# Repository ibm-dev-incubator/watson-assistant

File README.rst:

Watson Home Assistant Raspberry Pi Hat
======================================

This project is a raspberry pi hat that includes an audio codec with an
integrated microphone, speaker. The intent is to use this to leverage the Watson
APIs to create a voice controlled home assistant. In addition to the speakers
there are 4 addressable RGB LEDs that can be used for more user feedback.

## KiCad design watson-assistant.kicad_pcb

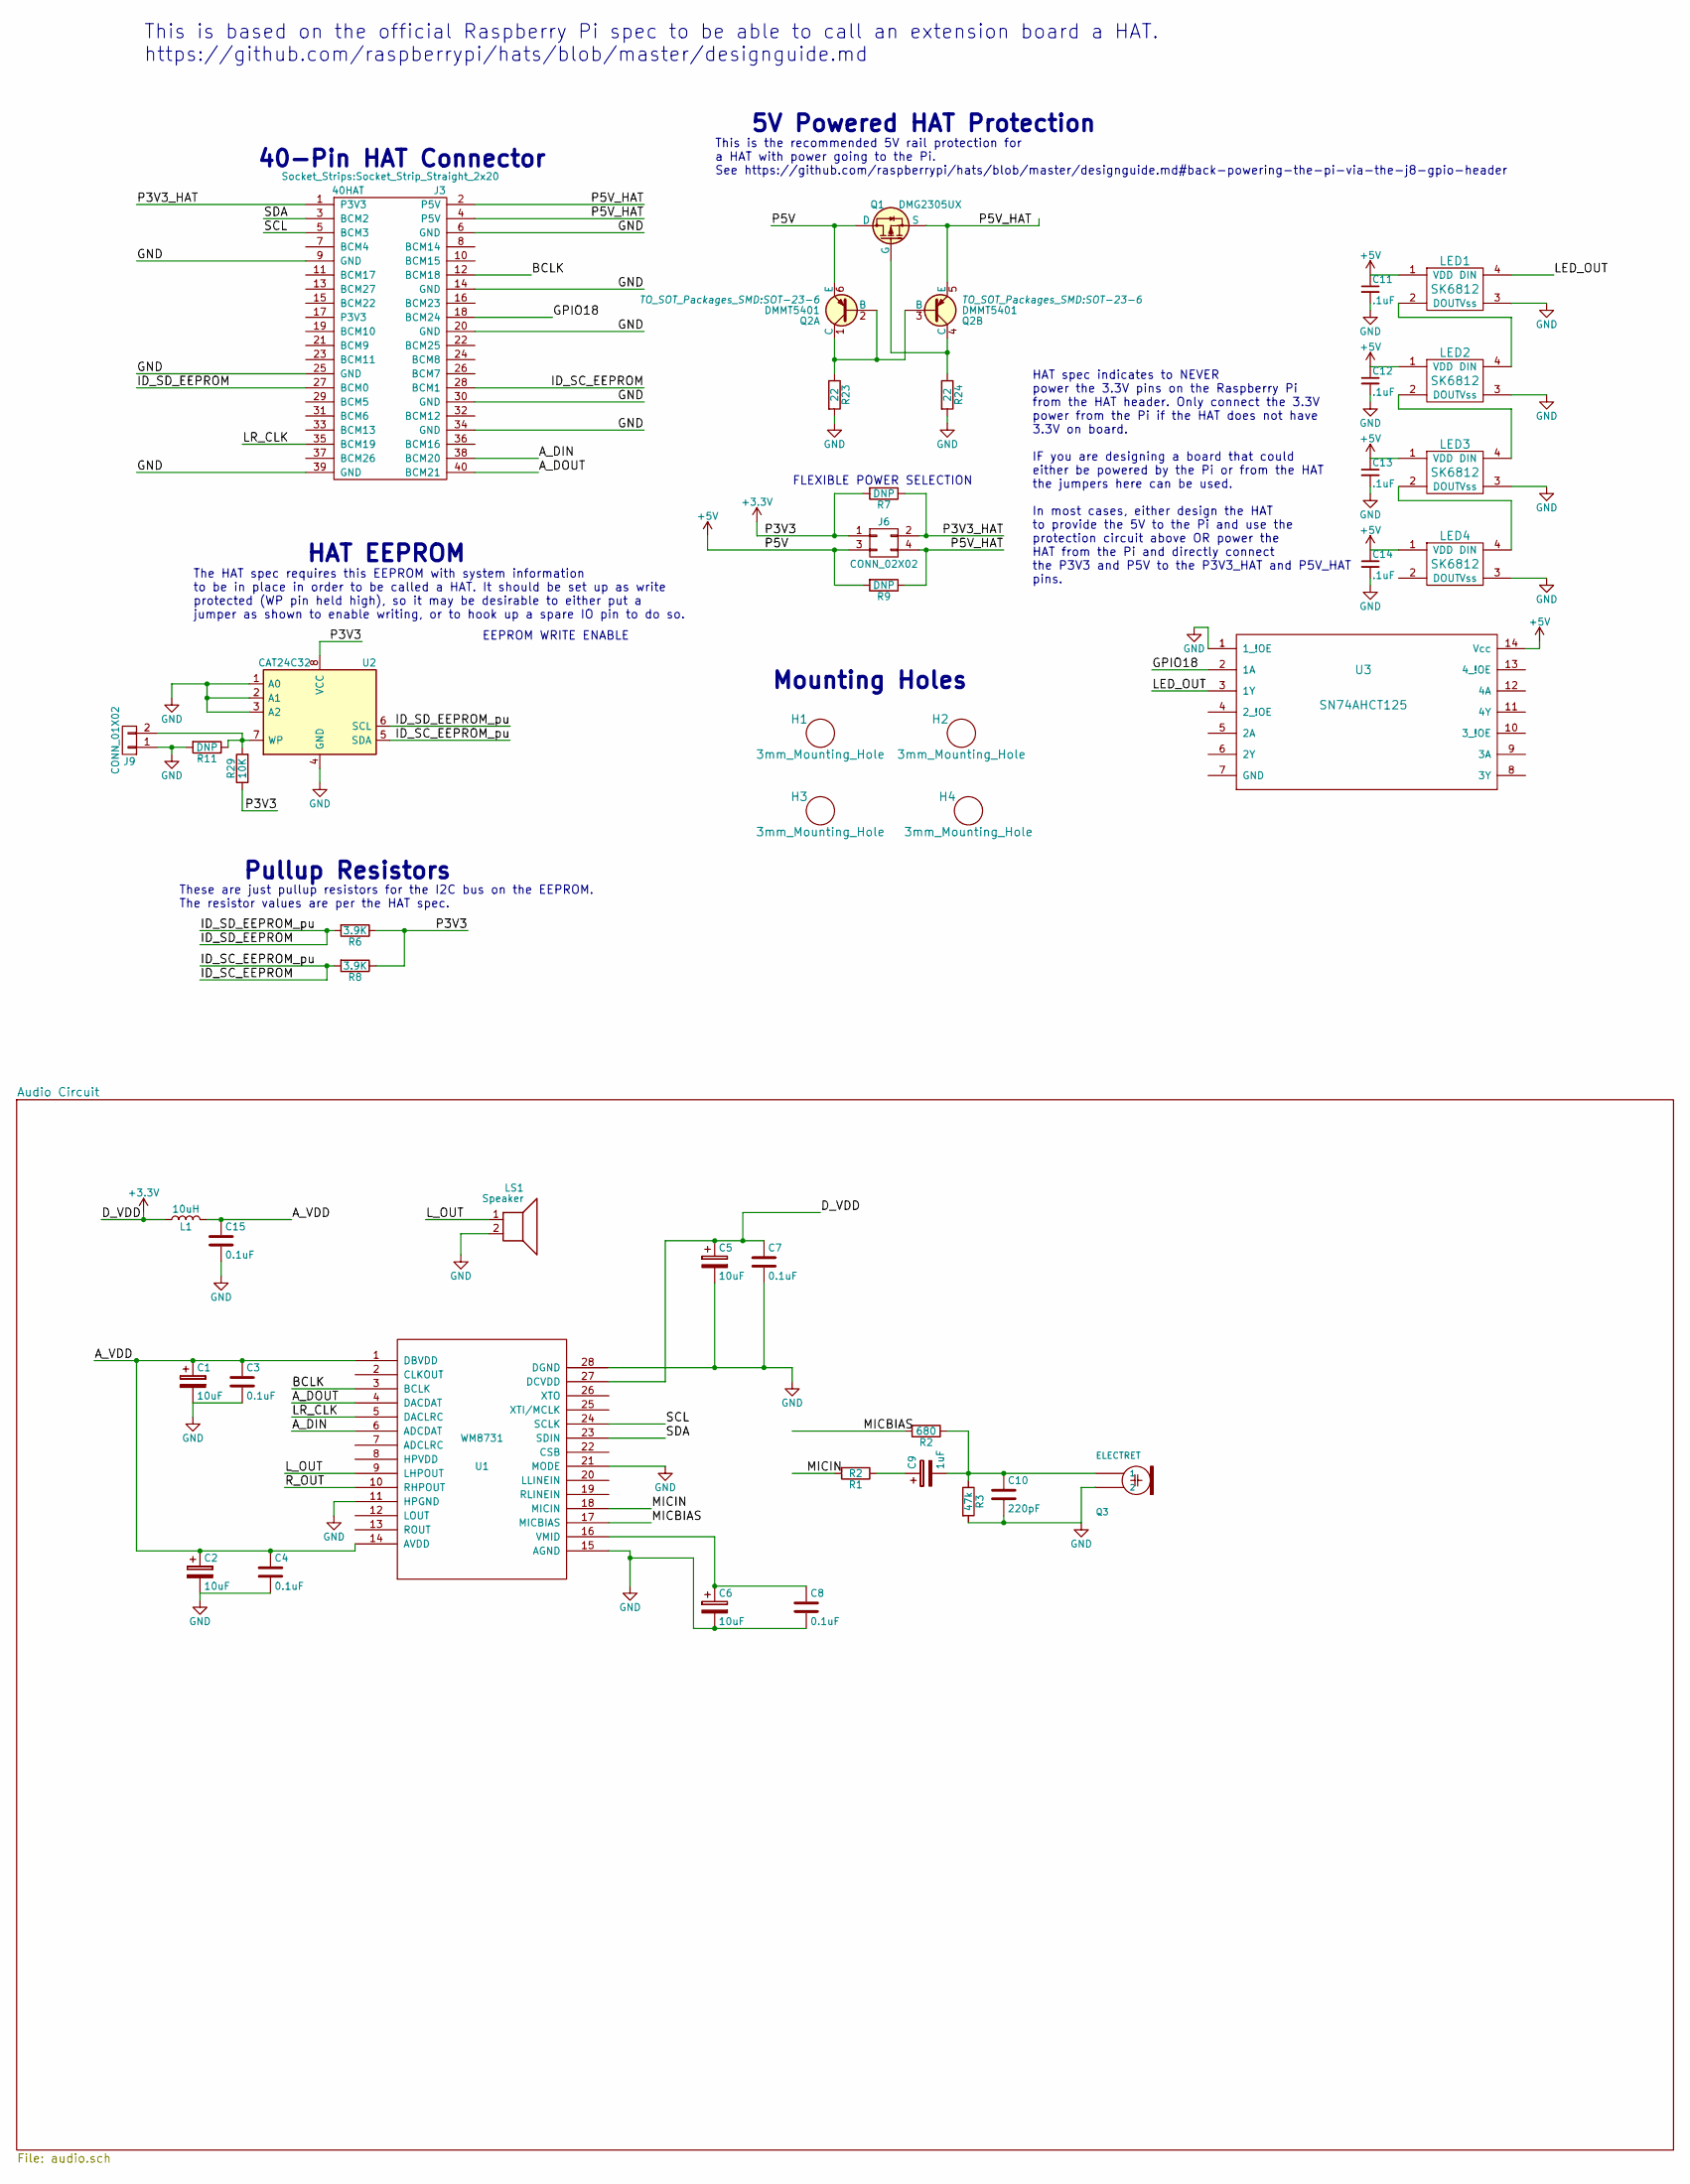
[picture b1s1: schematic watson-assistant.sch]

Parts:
C1, C2, C5, C6: 10uF; CP_Elec_5x4.5
C3, C4, C7, C8, C15: 0.1uF; C_0805_HandSoldering
C9: 1uF; CP_Elec_5x4.5
C10: 220pF; C_0805_HandSoldering
C11, C12, C13, C14: .1uF; C_0805_HandSoldering
H1, H2, H3, H4: 3mm_Mounting_Hole; NPTH_3mm_ID
J3: 40HAT; Socket_Strip_Straight_2x20
J6: CONN_02X02; Pin_Header_Straight_2x02
J9: CONN_01X02; Pin_Header_Straight_1x02
L1: 10uH; L_0805_HandSoldering
LED1, LED2, LED3, LED4: SK6812; WS2812B
LS1: Speaker; TerminalBlock_Pheonix_PT-3.5mm_2pol
Q1: DMG2305UX; SOT-23
Q2: DMMT5401; SOT-23-6
Q3: ELECTRET; 9.7ELECTRET
R1: R2; R_0603_HandSoldering
R2: 680; R_0603_HandSoldering
R3: 47k; R_0603_HandSoldering
R6, R8: 3.9K; R_0603_HandSoldering; MPN RC0402JR-0722RL
R7, R9, R11: DNP; R_0805_HandSoldering; MPN RC0402JR-0722RL
R23, R24: 22; R_0603_HandSoldering; MPN RC0402JR-0722RL
R29: 10K; R_0603_HandSoldering; MPN RC0402JR-0722RL
U1: WM8731; SSOP-28_5.3x10.2mm_Pitch0.65mm
U2: CAT24C32; SOIC-8_3.9x4.9mm_Pitch1.27mm
U3: SN74AHCT125; DIP-14_W7.62mm_LongPads

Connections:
+3V3: C5.1, C7.1, J6.1, L1.1, R6.1, R7.2, R8.1, R29.1, U1.27 (DCVDD), U2.8 (VCC)
+5V: C11.1, C12.1, C13.1, C14.1, J6.3, LED1.1 (VDD), LED2.1 (VDD), LED3.1 (VDD), LED4.1 (VDD), Q1.3 (D), Q2.6 (E), R9.2, U3.14 (Vcc)
/A_DIN: J3.38 (BCM20), U1.6 (ADCDAT)
/A_DOUT: J3.40 (BCM21), U1.4 (DACDAT)
/A_VDD: C1.1, C2.1, C3.1, C4.1, C15.1, L1.2, U1.1 (DBVDD), U1.14 (AVDD)
/BCLK: J3.12 (BCM18), U1.3 (BCLK)
/GPIO18: J3.18 (BCM24), U3.2 (1A)
/ID_SC_EEPROM: J3.28 (BCM1), R8.2, U2.5 (SDA)
/ID_SD_EEPROM: J3.27 (BCM0), R6.2, U2.6 (SCL)
/LED_OUT: LED1.4 (DIN), U3.3 (1Y)
/LR_CLK: J3.35 (BCM19), U1.5 (DACLRC)
/L_OUT: LS1.1, U1.9 (LHPOUT)
/MICBIAS: R2.2, U1.17 (MICBIAS)
/MICIN: R1.2, U1.18 (MICIN)
/P3V3_HAT: J3.1 (P3V3), J6.2, R7.1
/P5V_HAT: J3.2 (P5V), J3.4 (P5V), J6.4, Q1.2 (S), Q2.5 (E), R9.1
/R_OUT: U1.10 (RHPOUT)
/SCL: J3.5 (BCM3), U1.24 (SCLK)
/SDA: J3.3 (BCM2), U1.23 (SDIN)
GND: C1.2, C2.2, C3.2, C4.2, C5.2, C6.2, C7.2, C8.2, C10.2, C11.2, C12.2, C13.2, C14.2, C15.2, J3.6 (GND), J3.9 (GND), J3.14 (GND), J3.20 (GND), J3.25 (GND), J3.30 (GND), J3.34 (GND), J3.39 (GND), J9.1, LED1.3 (Vss), LED2.3 (Vss), LED3.3 (Vss), LED4.3 (Vss), LS1.2, Q3.+ (2), R3.2, R11.2, R23.2, R24.2, U1.11 (HPGND), U1.15 (AGND), U1.21 (MODE), U1.28 (DGND), U2.1 (A0), U2.2 (A1), U2.3 (A2), U2.4 (GND), U3.1 (1_!OE)
unnamed: C6.1, C8.1, U1.16 (VMID)
unnamed: C9.1, R1.1
unnamed: C9.2, C10.1, Q3.- (1), R2.1, R3.1
unnamed: J9.2, R11.1, R29.2, U2.7 (WP)
unnamed: LED1.2 (DOUT), LED2.4 (DIN)
unnamed: LED2.2 (DOUT), LED3.4 (DIN)
unnamed: LED3.2 (DOUT), LED4.4 (DIN)
unnamed: Q1.1 (G), Q2.4 (C), R24.1
unnamed: Q2.1 (C), Q2.2 (B), Q2.3 (B), R23.1

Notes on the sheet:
FLEXIBLE POWER SELECTION
5V Powered HAT Protection
This is the recommended 5V rail protection for a HAT with power going to the Pi. See https://github.com/raspberrypi/hats/blob/master/designguide.md#back-powering-the-pi-via-the-j8-gpio-header
EEPROM WRITE ENABLE
Pullup Resistors
HAT EEPROM
Mounting Holes
40-Pin HAT Connector
HAT spec indicates to NEVER power the 3.3V pins on the Raspberry Pi from the HAT header. Only connect the 3.3V power from the Pi if the HAT does not have 3.3V on board. IF you are designing a board that could either be powered by the Pi or from the HAT the jumpers here can be used. In most cases, e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
The HAT spec requires this EEPROM with system information to be in place in order to be called a HAT. It should be set up as write protected (WP pin held high), so it may be desirable to either put a jumper as shown to enable writing, or to hook up a spare IO pin to do so.
These are just pullup resistors for the I2C bus on the EEPROM. The resistor values are per the HAT spec.
This is based on the official Raspberry Pi spec to be able to call an extension board a HAT. https://github.com/raspberrypi/hats/blob/master/designguide.md

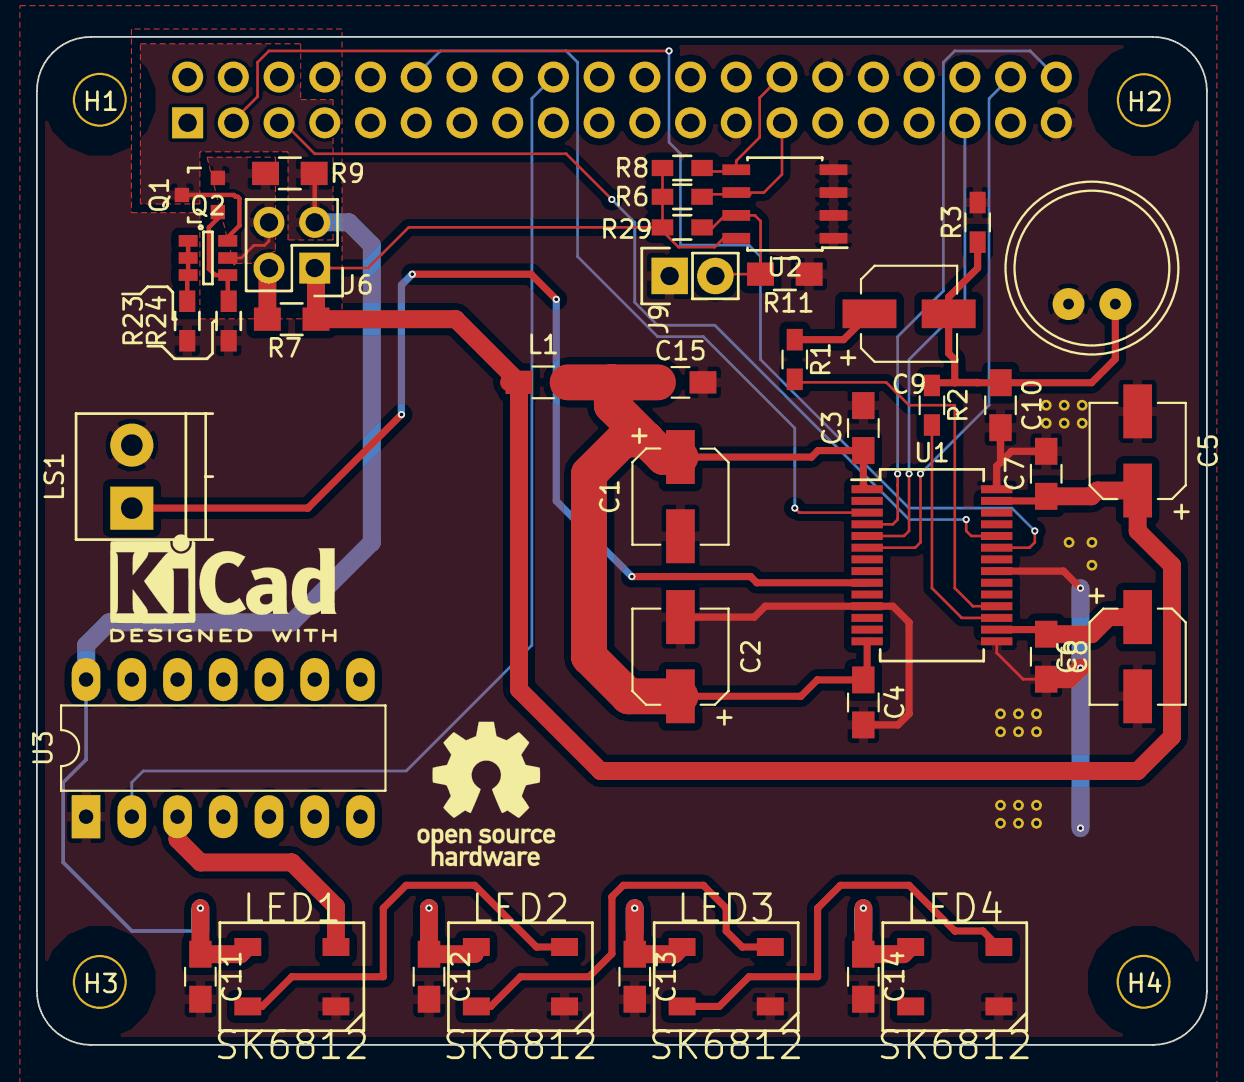
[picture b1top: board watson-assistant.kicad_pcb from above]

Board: 4 copper layers, 65.0 x 56.0 mm, 45 parts (1 on the bottom side), 28 nets.

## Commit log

2017-08-15 First version with all pcb nets connected
2017-08-15 Add silk screen logos
2017-08-15 Add supporting docs
2017-08-30 Add footprints for pcb mounted speakers
2017-08-30 Add terminal for speaker output
    This adds a terminal for a speaker. None of the commonly available pcb
    mount speakers fit on the hat board with all the other components, so
    this adds a terminal on the left edge to wire a speaker to.
2017-08-30 Remove pcb comment about smt header
